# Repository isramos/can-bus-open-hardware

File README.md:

# CAN Bus Open Hardware

Example code and drivers for open-source CAN bus hardware platforms.

Created to support classes at [canbusacademy.com](https://canbusacademy.com).

## Platforms

| Platform | MCU | CAN | Notes |
|----------|-----|-----|-------|
| [Arduino](arduino/) | ATmega | MCP2515 (external, SPI) | Needs shield or breakout |
| [ESP32](esp32/) | ESP32 | TWAI (built-in) | Needs external transceiver |
| [STM32](stm32/) | STM32F103+ | bxCAN (built-in) | CAN shares pins with USB on Blue Pill |
| [Teensy 4.x](teensy/) | i.MX RT1062 | FlexCAN (built-in, 3 buses) | Needs external transceiver |
| [Raspberry Pi](raspberry-pi/) | BCM2711/2712 | socketcan (kernel) | Via SPI HAT or USB adapter |

## Getting Started

Each platform folder has its own README with wiring, library dependencies, and defaults.

Every platform includes a simple send + receive example that sends a heartbeat frame and prints received frames.

All examples default to **250 kbps**.

## Hardware

Open-source PCB designs for CAN bus lab equipment, using the [CBA-CAN-TRS](hardware/CBA-CAN-TRS.md) connector spec (CAN bus over 3.5mm TRS audio jacks).

| Board | Description | Folder |
|-------|-------------|--------|
| [CAN Adapter](hardware/can-adapter/) | DB9 to 3x TRS breakout + termination | `hardware/can-adapter/` |
| [CAN Hub](hardware/can-hub/) | 6-port TRS passive CAN bus hub | `hardware/can-hub/` |

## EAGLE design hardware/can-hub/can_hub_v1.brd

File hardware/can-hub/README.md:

# CAN Hub

6-port [CBA-CAN-TRS](../CBA-CAN-TRS.md) passive CAN bus hub.

## Purpose

Connects up to 6 CAN nodes using 3.5mm stereo cables. All ports are wired in parallel — CAN_H to CAN_H, CAN_L to CAN_L, GND to GND.

Any platform with pin headers (Arduino, ESP32, STM32, Teensy, CANable) can connect directly — solder CAN_H, CAN_L, and GND to a TRS plug and plug into the hub. For DB9 devices, use the [CAN Adapter](../can-adapter/) board.

## Specs

- **Size**: 31.9 x 27.9 mm (2-layer)
- **Connectors**: 6x PJ-30220 (3.5mm TRRS jack)
- **Breakout header**: JP1 exposes all bus signals for probing
- **Passive** — no active components, no power required

## BOM

| Ref | Part | Value |
|-----|------|-------|
| J1–J6 | PJ-30220 | 3.5mm 4-pole audio jack |
| JP1 | Pin header | Bus breakout for probing |

## Files

- `can_hub_v1.sch` — Eagle schematic
- `can_hub_v1.brd` — Eagle board layout
- `gerbers/` — production-ready Gerber files

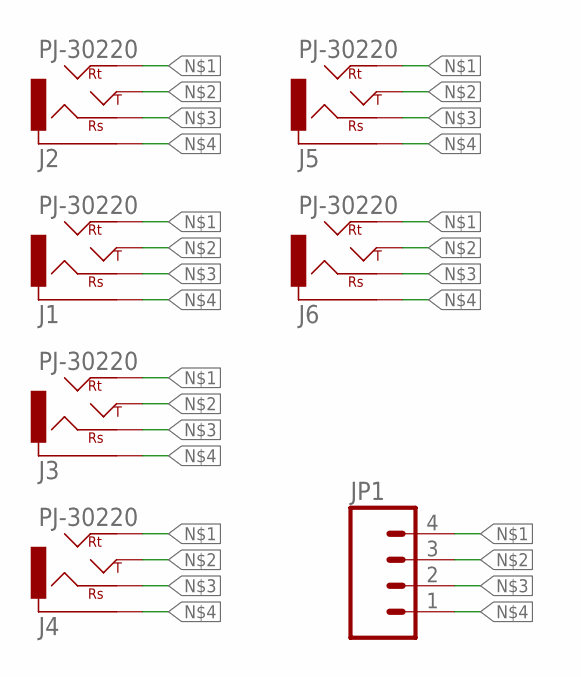
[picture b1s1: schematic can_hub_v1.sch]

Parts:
J1, J2, J3, J4, J5, J6: PJ-30220; PARTNO PJ30220
JP1: M04PTH; 1X04

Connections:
unnamed: J1.P$04 (RT), J2.P$04 (RT), J3.P$04 (RT), J4.P$04 (RT), J5.P$04 (RT), J6.P$04 (RT), JP1.4
unnamed: J1.P$03 (TIP), J1.P$03B (TIP), J2.P$03 (TIP), J2.P$03B (TIP), J3.P$03 (TIP), J3.P$03B (TIP), J4.P$03 (TIP), J4.P$03B (TIP), J5.P$03 (TIP), J5.P$03B (TIP), J6.P$03 (TIP), J6.P$03B (TIP), JP1.3
unnamed: J1.P$02 (RS), J2.P$02 (RS), J3.P$02 (RS), J4.P$02 (RS), J5.P$02 (RS), J6.P$02 (RS), JP1.2
unnamed: J1.P$01 (SLEEVE), J2.P$01 (SLEEVE), J3.P$01 (SLEEVE), J4.P$01 (SLEEVE), J5.P$01 (SLEEVE), J6.P$01 (SLEEVE), JP1.1

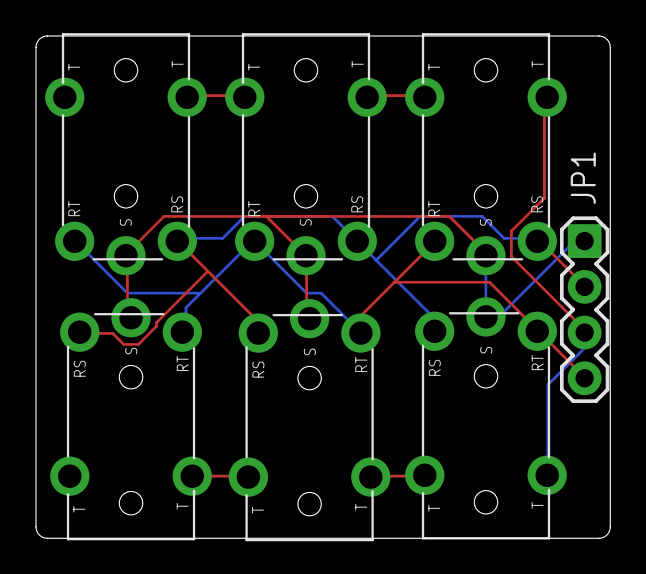
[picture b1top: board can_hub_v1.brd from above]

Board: 2 copper layers, 31.9 x 27.9 mm, 7 parts (0 on the bottom side), 4 nets.

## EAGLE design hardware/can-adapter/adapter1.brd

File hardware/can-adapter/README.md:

# CAN Adapter

DB9 to 3x [CBA-CAN-TRS](../CBA-CAN-TRS.md) breakout board with switchable termination.

## Purpose

Connects a standard DB9 CAN interface (vehicle, analyzer, or bench setup) to three CBA-CAN-TRS audio jack ports. Plug in up to 3 CAN tools or nodes using cheap 3.5mm stereo cables.

## Specs

- **Size**: 18.7 x 31.8 mm (2-layer)
- **Connectors**: 1x DB9 female, 3x PJ-30220 (3.5mm TRRS jack)
- **Termination**: 120 ohm resistor with solder jumper (RT). Standard CAN termination for one end of the bus. Alternatively, use 60 ohm for single-point termination (equivalent to two 120 ohm resistors in parallel) when only one endpoint is terminated.
- **Breakout header**: JP3 exposes CAN_H, CAN_L, GND for probing or external wiring
- **Passive** — no active components, no power required

## DB9 Pinout

This board uses the **Seeed/education convention**:

| DB9 Pin | Signal |
|---------|--------|
| 3 | CAN_H |
| 5 | CAN_L |
| 2 | GND |

**Warning:** This is NOT the CiA DS102 industry standard used by Microchip, PEAK, and Kvaser analyzers:

| DB9 Pin | CiA DS102 |
|---------|-----------|
| 7 | CAN_H |
| 2 | CAN_L |
| 3 | GND |

Do not cross-connect without verifying pinouts. A crossover cable or re-pinned adapter is needed to interface between the two conventions.

## BOM

| Ref | Part | Value |
|-----|------|-------|
| X1 | DB9 female | — |
| J1, J2, J3 | PJ-30220 | 3.5mm 4-pole audio jack |
| R1 | Resistor (0805) | 120 ohm (see note below) |
| RT, JP3 | Solder jumper | Termination enable |

## Files

- `db9_trs_adapter.sch` — Eagle schematic
- `db9_trs_adapter.brd` — Eagle board layout
- `gerbers/` — production-ready Gerber files

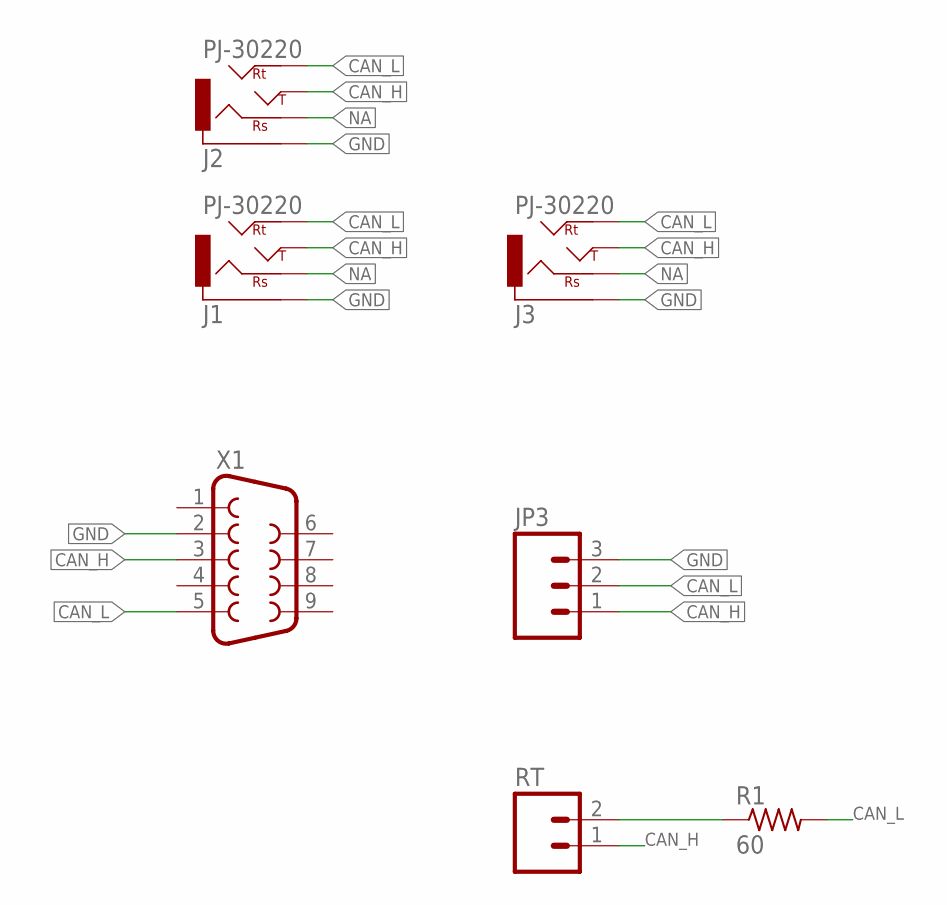
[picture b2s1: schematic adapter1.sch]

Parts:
J1, J2, J3: PJ-30220; PARTNO PJ30220
JP3: M03PTH; 1X03
R1: 60; M0805
RT: M02PTH; 1X02
X1: DB9FEMALE; DB9

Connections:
CAN_H: J1.P$03 (TIP), J1.P$03B (TIP), J2.P$03 (TIP), J2.P$03B (TIP), J3.P$03 (TIP), J3.P$03B (TIP), JP3.1, RT.1, X1.3
CAN_L: J1.P$04 (RT), J2.P$04 (RT), J3.P$04 (RT), JP3.2, R1.2, X1.5
GND: J1.P$01 (SLEEVE), J2.P$01 (SLEEVE), J3.P$01 (SLEEVE), JP3.3, X1.2
unnamed: R1.1, RT.2
NA: J1.P$02 (RS), J2.P$02 (RS), J3.P$02 (RS)

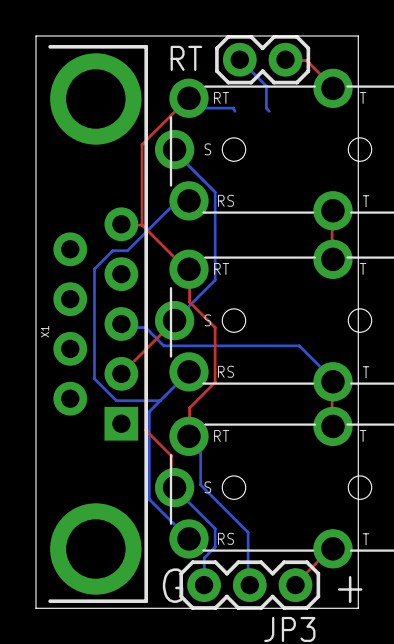
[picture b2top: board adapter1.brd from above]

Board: 2 copper layers, 17.9 x 31.8 mm, 7 parts (1 on the bottom side), 5 nets.

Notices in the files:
parts and their libraries:
SparkFun: Licensing: CC v3.0 Share-Alike You are welcome to use this library for commercial purposes.
